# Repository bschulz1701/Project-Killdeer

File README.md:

# Project-Killdeer
Hardware designs for a LED light string UPS

# Repo Outline
<!-- #### [Documents](Documents/) 

General document and image storage for repo and README -->

#### [Hardware](Hardware/)

Current board files (Eagle), Bill of Materials (BoM), and other design documents

#### [Production](Production/)

Contains the various Gerber and pick and place files required to have the Printed Circuit Boards (PCBs) manufactured or populated 

<!-- #### [Software](Software/)

The software associated with the piece of hardware, this is usually diagnostic software used for verifying or investigating the hardware

#### [Testing](Testing/)

Scripts and results from the testing process and development process. Contains more detailed information about documented issues among other testing.  -->

<!-- ## Overview
* **Type:** Data Logger/Daughterboard 
* **Interfaces:** I<sup>2</sup>C, GPIO, Pulse
* **Release Version:** v0.2 - 2020/07/15 -->

<!-- 

 -->

<!-- ## Features
### On-Board
* Micro SD Card 
* RTC w/Battery Backup
* Temperature/Pressure/RH Sensor
* RGB Ambient Light Sensor
* Reverse Polarity Power Protected Inputs 

### Interface
* Tipping Bucket Input (SPST switch compatible)
* Dedicated Potentiometric Input (x1) 
* Flexible Sensor Inputs (x3)
* Dedicated I<sup>2</sup>C Input (x1) 
* Supports Particle and other Feather based controllers 

## Specifications
* **Sensor Voltage:** 3.3V
* **Sensor Current (Max):** 500mA (Combined)

## Jumper Settings 

**Port Select Jumpers**
| Jumper | Purpose | Position 1 | Position 2 | 
| ------ | ------- | ---------- | ---------- |
| `JP1`	| GPIO vs I<sup>2</sup>C - Port 1 Digital | Select I2C | Select GPIO | 
| `JP2` | GPIO vs I<sup>2</sup>C - Port 1 Analog | Select I2C | Select GPIO | 
| `JP3` | GPIO vs I<sup>2</sup>C - Port 2 Digital | Select I2C | Select GPIO | 
| `JP4` | GPIO vs I<sup>2</sup>C - Port 2 Analog | Select I2C | Select GPIO | 
| `JP5` | GPIO vs I<sup>2</sup>C - Port 3 Digital | Select I2C | Select GPIO | 
| `JP6` | GPIO vs I<sup>2</sup>C - Port 3 Analog | Select I2C | Select GPIO | 
| `JP8` | Power Select (Core vs Ext) - Port 1 | Core Power for Port 1 | External Switched Power for Port 1 |

**Configuration Jumpers**
| Jumper | Purpose | Open | Closed | Default | 
| ------ | ------- | ---------- | ---------- | ----- | 
| `JP7` | Enable Hardware WDT | WDT Disabled | WDT Enabled | Closed |  
| `JP9` | Pullup for Port 1 Digital GPIO | Pullup Disabled | Pullup Enabled | Open |
| `JP10` | Gang On-Board and External I2C Buses | I2C Combined | I2C Isolated | Open | 

## Known Issues/Errata

#### WDT Disable

**Issue:** If using Particle Boron as controller and if you have the WDT disabled (leave `JP7` open), the system fails to run properly, or has sporadic resets. This is likely due to parasitic current on the reset line of the Boron.

**Workaround:** Make sure WDT is enabled by closing `JP7`

#### Solder Jumper Stencil

**Issue:** Depending on the thickness of the solder stencil used for populating the board, the solder jumpers may not bridge when desired. This is due to lack of stencil thickness specification and pad geometry.

**Workaround:** Make a note on the board assembly (if working with a board house) as to which jumpers should be connected (see jumper tables). Otherwise, if assembling manually, check the jumpers are connected, and bridge them using solder wire and a soldering iron if they have failed to jump where desired. 
 -->

## Specifications (3S1P)
* Input Voltage (DC Input): 9V ~ 12V
* Input Current (DC Input): 250mA, min
* Low Battery Indication: 2.48V (~ 0.825V/Cell)

**Quiescent Current Values**
| Battery | DC Input | System State | Low Battery | Current Battery | Current DC Input |
| ------- | -------- | ------------ | ----------- | --------------- | ---------------- |
| 4.5V | 0V | Off | NO | 3.25&mu;A | 0A |
| 4.5V | 0V | On | NO | 4.35&mu;A | 0A |
| 4.5V | 9V | Off | NO | 2.22&mu;A | 10.67mA |
| 4.5V | 9V | On | NO | 2.69&mu;A | 10.67mA |  
| 2V | 9V | Off | YES | 0.97&mu;A| 10.98mA | 
| 2V | 9V | On | YES | 1.42&mu;A | 10.98mA |

## Known Issues/Errata
**3S1P, v0.0:**
* Silkscreen above DC input plug lists voltage range as "5V ~ 12V", if input is less than 7.5V, full output voltage will not be achieved 
* If battery voltage falls below ~ 2V (~ 0.65V/Cell) **and** there is no DC input, the low battery light will not iluminate

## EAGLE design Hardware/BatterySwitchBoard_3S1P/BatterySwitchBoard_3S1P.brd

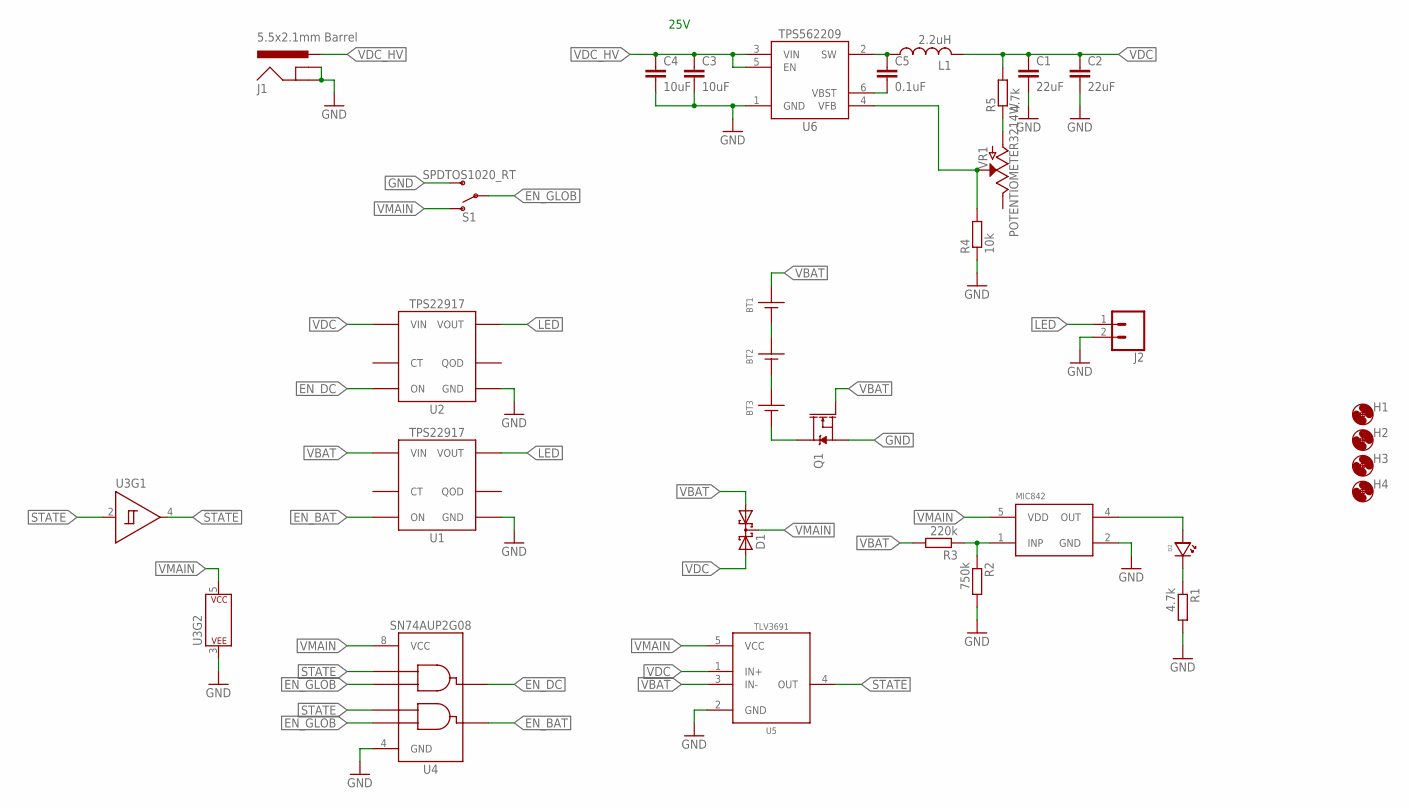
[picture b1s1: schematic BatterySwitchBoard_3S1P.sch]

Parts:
BT1, BT2, BT3: AACLIP; BAT_AA
C1, C2: 22uF; C0805
C3, C4: 10uF; C0805
C5: 0.1uF; C0603
D1: DIODE_CCBAT54CSOT23; SOT23-3
D2: LED0603; LED_0603
H1, H2, H3, H4: MOUNTING_HOLE4_NP; 4_40
J1: 5.5x2.1mm Barrel; POWER_JACK_SMD
J2: CONN_023.5MM_ROUND_RESTRICT; SCREWTERMINAL-3.5MM-2_ROUND_RESTRICT
L1: 2.2uH; 1008
Q1: DMG3404; SOT23-3
R1, R5: 4.7k; R0603
R2: 750k; R0603
R3: 220k; R0603
R4: 10k; R0603
S1: SPDTOS1020_RT; OS102011MA1QN1
U1, U2: TPS22917DBV; DBV_R-PDSO-G6
U3: SN74AUP1G14DCK; DCK_R-PDSO-G5
U4: SN74AUP2G08DCU; DCU_(S-PDSO-G8)
U5: TLV3691DCK; DCK_R-PDSO-G5
U6: TPS56209; DDC_R-PDSO-G6
U7: MIC842L; DCK_R-PDSO-G5
VR1: POTENTIOMETER3214W; POT_3214W

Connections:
!STATE: U3.4 (Y), U4.5 (A2)
EN_BAT: U1.3 (ON), U4.3 (Y2)
EN_DC: U2.3 (ON), U4.7 (Y1)
EN_GLOB: S1.2, U4.2 (B1), U4.6 (B2)
GND: C1.2, C2.2, C3.2, C4.2, J1.GND (GNDBREAK), J1.P$4 (GND), J2.2, Q1.2 (S), R1.2, R2.2, R4.1, S1.3 (S), U1.2 (GND), U2.2 (GND), U3.3 (P$V-), U4.4 (GND), U5.2 (GND), U6.1 (GND), U7.2 (GND)
LED: J2.1, U1.6 (VOUT), U2.6 (VOUT)
unnamed: BT1.NEG@1 (-), BT1.NEG@2 (-), BT2.POS@1 (+), BT2.POS@2 (+)
unnamed: R2.1, R3.1, U7.1 (INP)
unnamed: BT3.NEG@1 (-), BT3.NEG@2 (-), Q1.3 (D)
unnamed: D2.ANODE, U7.4 (OUT)
unnamed: C5.1, L1.1, U6.2 (SW)
unnamed: D2.CATHODE, R1.1
unnamed: C5.2, U6.6 (VBST)
unnamed: R4.2, U6.4 (VFB), VR1.2 (S)
unnamed: BT2.NEG@1 (-), BT2.NEG@2 (-), BT3.POS@1 (+), BT3.POS@2 (+)
unnamed: R5.1, VR1.1 (A)
QOD: U1.5 (QOD), U2.5 (QOD)
STATE: U3.2 (A), U4.1 (A1), U5.4 (OUT)
VBAT: BT1.POS@1 (+), BT1.POS@2 (+), D1.1 (A1), Q1.1 (G), R3.2, U1.1 (VIN), U5.3 (IN-)
VDC: C1.1, C2.1, D1.2 (A2), L1.2, R5.2, U2.1 (VIN), U5.1 (IN+)
VDC_HV: C3.1, C4.1, J1.VIN0 (PWR), U6.3 (VIN), U6.5 (EN)
VMAIN: D1.3 (C), S1.1 (O), U3.5 (P$V+), U4.8 (VCC), U5.5 (VCC), U7.5 (VDD)

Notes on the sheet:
25V

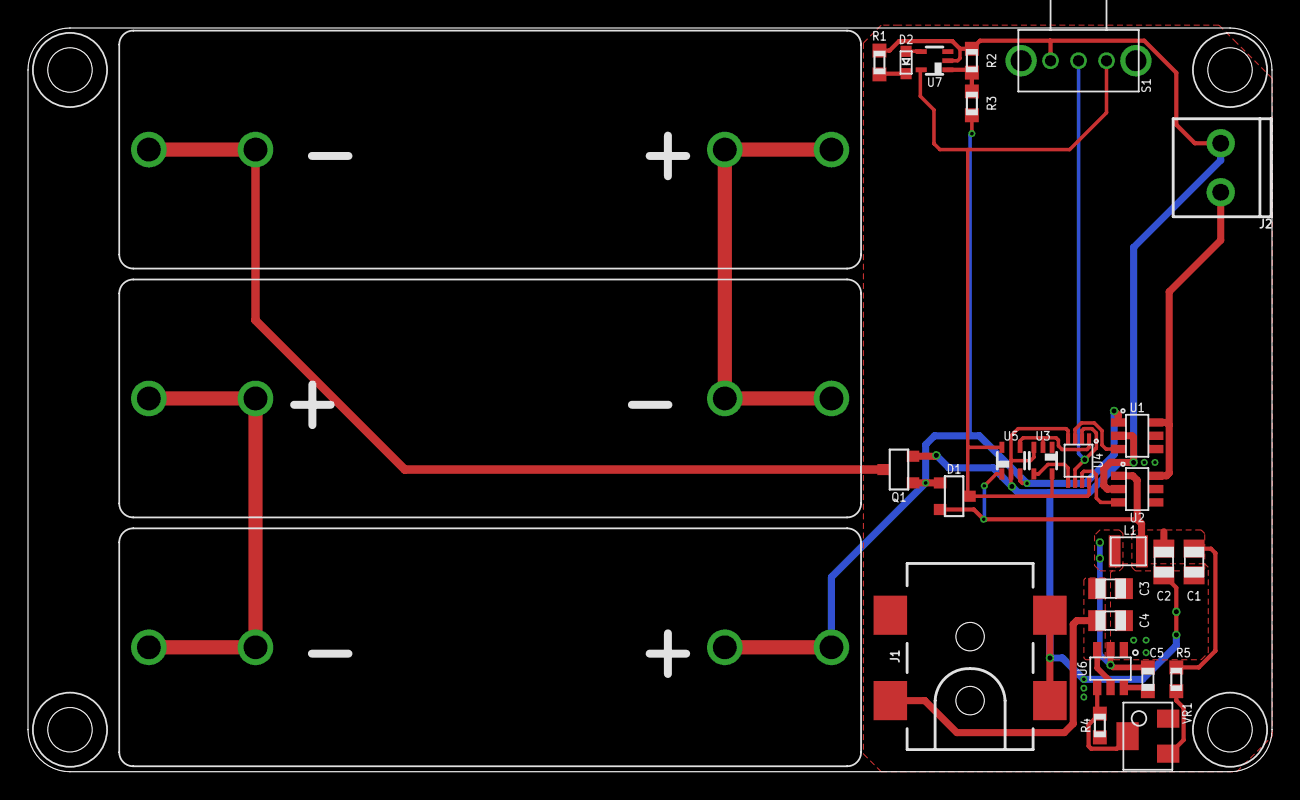
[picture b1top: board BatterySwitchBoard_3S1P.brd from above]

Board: 2 copper layers, 88.9 x 53.1 mm, 32 parts (0 on the bottom side), 22 nets.

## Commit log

2021-10-22 Added LICENSE and adjusted readme for folder system
2021-10-22 Added original Killdeer 2S1P module
2021-10-22 Added 3S1P design, sent to fab
2024-11-02 Added documentation and minor board updates
